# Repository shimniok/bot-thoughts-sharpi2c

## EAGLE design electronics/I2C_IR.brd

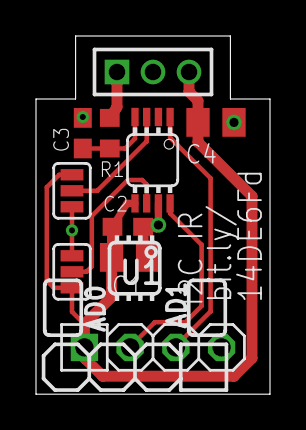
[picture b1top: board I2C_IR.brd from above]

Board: 2 copper layers, 13.0 x 19.9 mm, 10 parts (0 on the bottom side), 8 nets.

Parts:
C1: 4.7uF; C0805K
C2: 0.1uF; C0603
C3: 470pF; C0603
C4: 10uF; C0805K
JP1: MCU; 1X04-S
JP3: Sharp Module; 1X03M
R1: 22; R0603
SJ1: AD0; SJ_3
SJ2: AD1; SJ_3
U1: ADC081C021; MSOP8_0.65

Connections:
ADR0: SJ1.2, U1.3
ADR1: SJ2.2, U1.6
GND: C1.2, C2.2, C3.2, C4.2, JP1.4, JP3.2, SJ1.3, SJ2.3, U1.7
unnamed: C3.1, R1.1, U1.4
SCL: JP1.3, U1.1
SDA: JP1.2, U1.8
SIG: JP3.1, R1.2
VCC: C1.1, C2.1, C4.1, JP1.1, JP3.3, SJ1.1, SJ2.1, U1.5

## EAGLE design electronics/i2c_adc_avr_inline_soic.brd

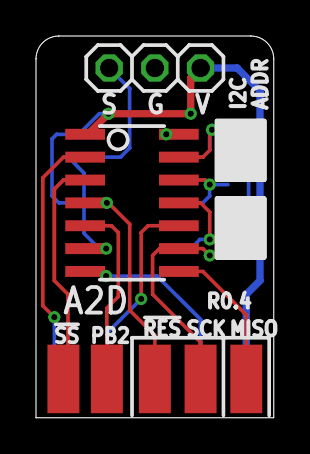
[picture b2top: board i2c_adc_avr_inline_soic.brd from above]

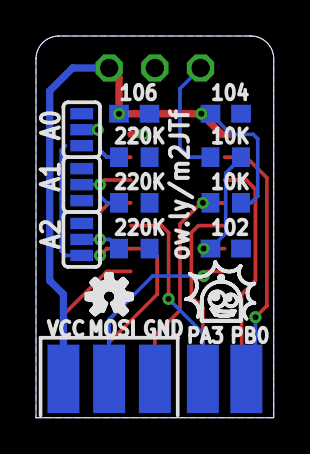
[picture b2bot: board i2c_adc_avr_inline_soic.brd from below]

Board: 2 copper layers, 13.2 x 21.2 mm, 18 parts (13 on the bottom side), 15 nets.

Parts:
A0, A1, A2: SJ_3
C2: 104; C0603
C3: 102; C0603
C4: 106; C0603
IC1: TINY24/44/84-SSU; SOIC14
J1: AVRISP62LAYER; 2X3_2LAYER
JP8: SENS; 1X03-S
R0, R1, R2: 220K; R0603
R3, R4: 10K; R0603
X1: PB2; PAD0.07X0.15
X2: !SS; PAD0.07X0.15
X3: PB0; PAD0.07X0.15
X4: PA3; PAD0.07X0.15

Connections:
!RESET: IC1.4, J1.!RES, R3.1
!SS: IC1.3, X2.P$1
A0: A0.2, IC1.13, R0.2
A1: A1.2, IC1.12, R1.2
A2: A2.2, IC1.11, R2.2
AIN: C3.1, IC1.6, R4.1
GND: A0.1, A1.1, A2.1, C2.2, C3.2, C4.2, IC1.14, J1.GND, JP8.2, R0.1, R1.1, R2.1
unnamed: JP8.1, R4.2
unnamed: IC1.10, X4.P$1
unnamed: IC1.2, X3.P$1
unnamed: IC1.5, X1.P$1
RX/SDA/MOSI: IC1.7, J1.MOSI
SCL/SCK: IC1.9, J1.SCK
TX/MISO: A0.3, A1.3, A2.3, IC1.8, J1.MISO
VCC: C2.1, C4.1, IC1.1, J1.VCC, JP8.3, R3.2

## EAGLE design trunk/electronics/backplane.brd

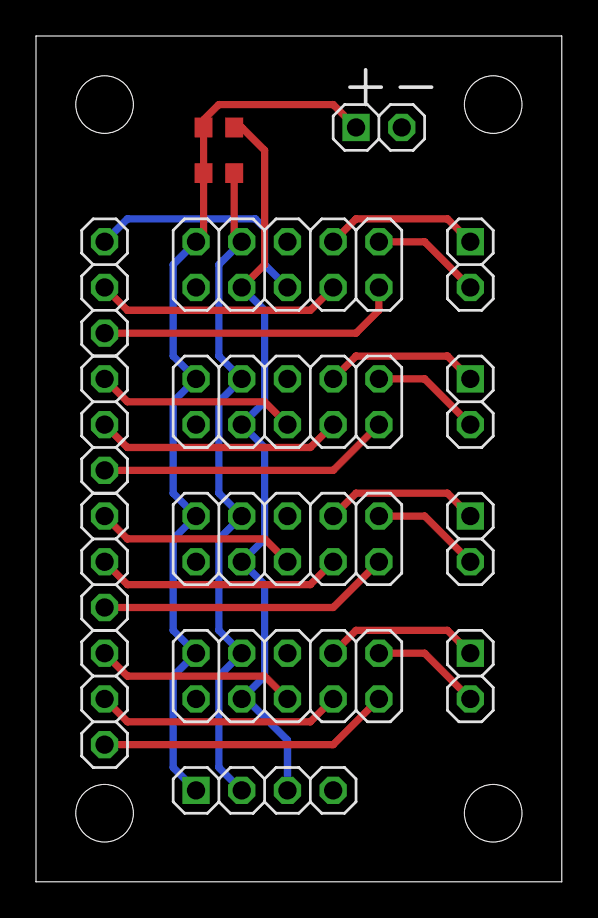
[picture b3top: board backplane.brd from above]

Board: 2 copper layers, 29.2 x 47.0 mm, 16 parts (0 on the bottom side), 24 nets.

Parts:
JP1, JP2, JP3, JP4: 2X05
JP5: PWR; 1X02-S
JP6, JP7, JP8, JP9: 1X02-S
JP10, JP11, JP12, JP13: 1X03-S
JP14: I2C; 1X04-S
R1, R2: 4.7k; R0603

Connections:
GND: JP1.6, JP2.6, JP3.6, JP4.6, JP5.2, JP14.4
unnamed: JP1.5, JP10.1
unnamed: JP1.7, JP10.2
unnamed: JP1.9, JP10.3
unnamed: JP1.8, JP6.1
unnamed: JP2.5, JP11.1
unnamed: JP2.7, JP11.2
unnamed: JP2.9, JP11.3
unnamed: JP3.5, JP12.1
unnamed: JP3.7, JP12.2
unnamed: JP3.9, JP12.3
unnamed: JP4.5, JP13.1
unnamed: JP4.7, JP13.2
unnamed: JP4.9, JP13.3
unnamed: JP1.10, JP6.2
unnamed: JP2.8, JP7.1
unnamed: JP2.10, JP7.2
unnamed: JP3.8, JP8.1
unnamed: JP3.10, JP8.2
unnamed: JP4.8, JP9.1
unnamed: JP4.10, JP9.2
SCL: JP1.3, JP2.3, JP3.3, JP4.3, JP14.3, R1.1
SDA: JP1.4, JP2.4, JP3.4, JP4.4, JP14.2, R2.2
VCC: JP1.2, JP2.2, JP3.2, JP4.2, JP5.1, JP14.1, R1.2, R2.1

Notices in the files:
parts and their libraries:
SparkFun: Licensing: CC v3.0 Share-Alike You are welcome to use this library for commercial purposes.
